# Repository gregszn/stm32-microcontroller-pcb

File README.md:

# STM32 Microcontroller PCB Design

## Overview

A two-layer STM32 microcontroller PCB designed using KiCad as a hardware design project.

The board integrates an STM32G431 microcontroller, USB connectivity, 3.3V voltage regulation, an external crystal oscillator, SWD programming/debugging, and peripheral interfaces.

This project combines schematic capture, component selection, PCB layout, signal routing, power distribution, and design rule verification.

The design was developed with guidance from Phil's Lab's STM32 PCB design tutorial.

## Technologies & Tools

- **EDA Software:** KiCad 10
- **Microcontroller:** STM32G431 ARM Cortex-M4
- **Voltage Regulation:** AMS1117-3.3 linear regulator
- **Communication Interfaces:** USB, UART
- **Programming and Debugging:** SWD interface
- **PCB Design:** Two-layer PCB, copper pours, vias, and signal routing
- **Design Verification:** KiCad Design Rules Checker (DRC)
- **Visualization:** KiCad 3D Viewer and STEP models

## System Architecture

The PCB integrates the microcontroller with supporting power, clock, communication, and debugging circuitry.

1. **Power Input:** The USB connector provides a 5V input supply.
2. **Voltage Regulation:** The AMS1117-3.3 regulator converts the input voltage into a regulated 3.3V supply.
3. **Microcontroller:** The STM32G431 operates using the regulated power supply.
4. **Clock Circuit:** An external crystal oscillator provides a clock reference.
5. **USB Communication:** USB D+ and D− signals connect to the microcontroller.
6. **Programming and Debugging:** SWD connections provide access for programming and debugging.
7. **Peripheral Interfaces:** Header connections expose UART, GPIO, power, and ground signals.

## Key Features

- STM32G431 ARM Cortex-M4 microcontroller
- USB-powered 3.3V voltage regulation
- External crystal oscillator circuit
- USB data signal routing
- SWD programming and debugging interface
- UART and peripheral header connections
- BOOT selection switch and reset circuitry
- Power indicator LED
- Two-layer PCB layout with copper pours
- Four mounting holes for mechanical integration

## Technical Implementation

### Power Supply Design

The PCB uses an AMS1117-3.3 linear regulator to convert the USB 5V supply into a regulated 3.3V output.

Input and output capacitors support voltage stability and filtering.

Decoupling capacitors are placed near the STM32 power pins to support stable operation.

### Microcontroller and Clock Circuit

The STM32G431 serves as the central processing component.

An external crystal oscillator and supporting capacitors provide an external clock reference.

The design also includes reset and BOOT circuitry for microcontroller configuration.

### USB and Debugging Interfaces

The USB connector provides power and routes USB D+ and D− signals to the STM32.

An SWD interface provides connections for external programming and debugging equipment.

Additional headers expose UART and peripheral signals for future hardware development.

### PCB Layout and Routing

The board was designed using a two-layer PCB stackup in KiCad.

Components were positioned to reduce routing complexity while maintaining access to the USB connector, debugging connections, and peripheral headers.

Signal and power traces were routed using copper tracks and vias.

Copper zones were added to provide electrical connectivity and support power distribution.

## Challenges and Troubleshooting

One of the main challenges was routing signals around the STM32 microcontroller while maintaining sufficient clearance between neighboring traces, pads, and vias.

During PCB verification, KiCad's Design Rules Checker identified several issues, including:

- Via diameters below the configured minimum
- Insufficient clearance between traces and vias
- Incomplete electrical connections
- Silkscreen markings extending beyond the PCB edge

These issues were addressed by adjusting via dimensions, repositioning vias, completing electrical connections, and modifying silkscreen elements.

The project also required careful placement of the USB connector to align its footprint with the physical PCB edge.

After these adjustments, the design passed the electrical routing checks with no clearance errors or unconnected items.

## Hardware Implementation

### 3D PCB Visualization

**Front View**

**Back View**

### PCB Layout

### Circuit Schematic

## Results

The completed design includes the STM32 microcontroller, regulated power supply, USB interface, external clock circuitry, debugging connections, and peripheral headers.

The PCB layout was completed in KiCad, and the final routing checks reported:

- Zero electrical clearance errors
- Zero unconnected items
- Completed power and signal routing
- Front and back 3D PCB visualizations

The project provided practical experience in schematic development, PCB routing, component footprint management, copper zone configuration, and design rule verification.

**The project is currently at the design stage. Physical PCB fabrication, assembly, and hardware testing have not yet been performed.**

## Project Files

- `STM32 PCB.kicad_pro` — KiCad project configuration
- `STM32 PCB.kicad_sch` — Circuit schematic
- `STM32 PCB.kicad_pcb` — PCB layout
- `images/` — PCB renders, layout, and schematic screenshots

## Future Improvements

- Fabricate and assemble the PCB.
- Verify the regulated 3.3V power supply.
- Test STM32 programming and debugging through SWD.
- Validate USB communication and UART functionality.
- Develop embedded firmware for peripheral testing.
- Perform hardware measurements using an oscilloscope and digital multimeter.
- Evaluate power integrity and signal quality.

## Reference

This project was developed as a tutorial-guided PCB design exercise using the following resource:

**Phil's Lab — KiCad 6 STM32 PCB Design Full Tutorial (#65)**

https://www.youtube.com/watch?v=aVUqaB0IMh4

The tutorial provided guidance on STM32 circuit architecture, schematic development, component placement, and PCB routing.

## License

This project is licensed under the MIT License.

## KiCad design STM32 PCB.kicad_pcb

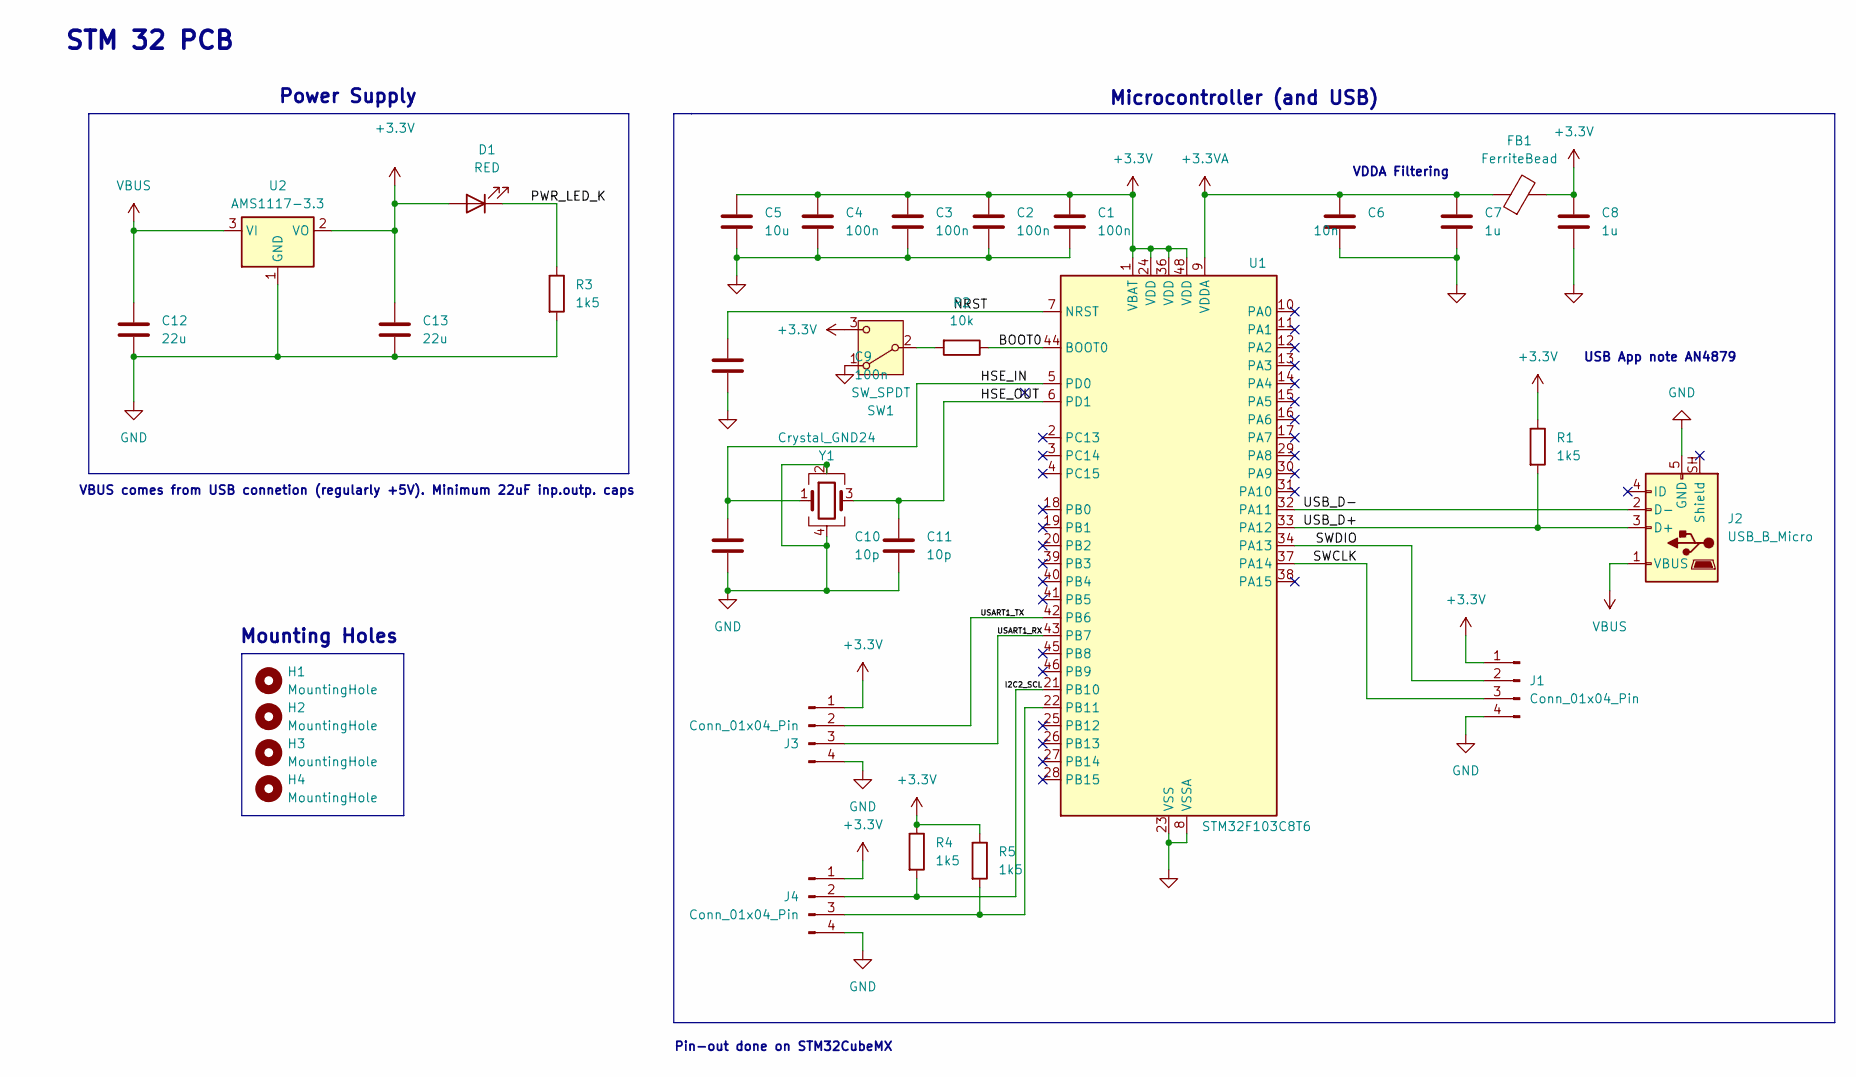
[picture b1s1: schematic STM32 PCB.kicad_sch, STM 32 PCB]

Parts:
C1, C2, C3, C4, C9: 100n; C_0402_1005Metric
C5: 10u; C_0603_1608Metric
C6: 10n; C_0402_1005Metric
C7, C8: 1u; C_0402_1005Metric
C10, C11: 10p; C_0402_1005Metric
C12, C13: 22u; C_0805_2012Metric
D1: RED; LED_0603_1608Metric
FB1: FerriteBead; L_0603_1608Metric
H1, H2, H3, H4: MountingHole; MountingHole_2.2mm_M2
J1, J3, J4: Conn_01x04_Pin; PinHeader_1x04_P2.54mm_Vertical
J2: USB_B_Micro; USB_Micro-B_Wuerth_629105150521
R1, R3, R4, R5: 1k5; R_0402_1005Metric
R2: 10k; R_0402_1005Metric
SW1: SW_SPDT; SW_SPDT_PCM12
U1: STM32F103C8T6; LQFP-48_7x7mm_P0.5mm
U2: AMS1117-3.3; SOT-223-3_TabPin2
Y1: Crystal_GND24; Crystal_SMD_3225-4Pin_3.2x2.5mm

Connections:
+3.3V: C1.1, C2.1, C3.1, C4.1, C5.1, C8.1, C13.1, D1.2 (A), FB1.2, J1.1, J3.1, J4.1, R1.1, R4.1, R5.1, SW1.3 (C), U1.1 (VBAT), U1.24 (VDD), U1.36 (VDD), U1.48 (VDD), U2.2 (VO)
+3.3VA: C6.1, C7.1, FB1.1, U1.9 (VDDA)
/BOOT0: R2.1, U1.44 (BOOT0)
/HSE_IN: C10.1, U1.5 (PD0), Y1.1
/HSE_OUT: C11.1, U1.6 (PD1), Y1.3
/I2C2_SCL: J4.2, R4.2, U1.21 (PB10)
/NRST: C9.1, U1.7 (NRST)
/PWR_LED_K: D1.1 (K), R3.1
/SWCLK: J1.3, U1.37 (PA14)
/SWDIO: J1.2, U1.34 (PA13)
/USART1_RX: J3.3, U1.43 (PB7)
/USART1_TX: J3.2, U1.42 (PB6)
/USB_D+: J2.3 (D+), R1.2, U1.33 (PA12)
/USB_D-: J2.2 (D-), U1.32 (PA11)
GND: C1.2, C2.2, C3.2, C4.2, C5.2, C6.2, C7.2, C8.2, C9.2, C10.2, C11.2, C12.2, C13.2, J1.4, J2.5 (GND), J3.4, J4.4, R3.2, SW1.1 (A), U1.8 (VSSA), U1.23 (VSS), U1.35 (VSS), U1.47 (VSS), U2.1 (GND), Y1.2 (G), Y1.4 (G)
unnamed: J4.3, R5.2, U1.22 (PB11)
unnamed: R2.2, SW1.2 (B)
VBUS: C12.1, J2.1 (VBUS), U2.3 (VI)

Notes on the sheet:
Microcontroller (and USB)
Pin-out done on STM32CubeMX
VDDA Filtering
STM 32 PCB
USB App note AN4879
Mounting Holes
VBUS comes from USB connetion (regularly +5V). Minimum 22uF inp.outp. caps
Power Supply

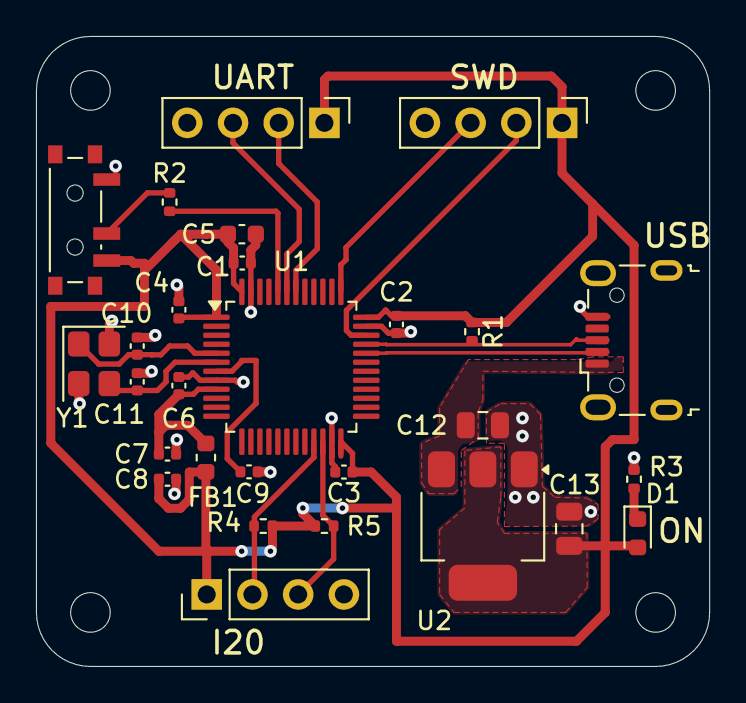
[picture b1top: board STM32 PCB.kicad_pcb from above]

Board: 2 copper layers, 37.4 x 35.0 mm, 32 parts (0 on the bottom side), 18 nets.
